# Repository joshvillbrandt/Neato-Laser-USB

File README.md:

Neato-Laser-USB
===============

A small PCB to run the Neato XV-11 laser scanner from USB.

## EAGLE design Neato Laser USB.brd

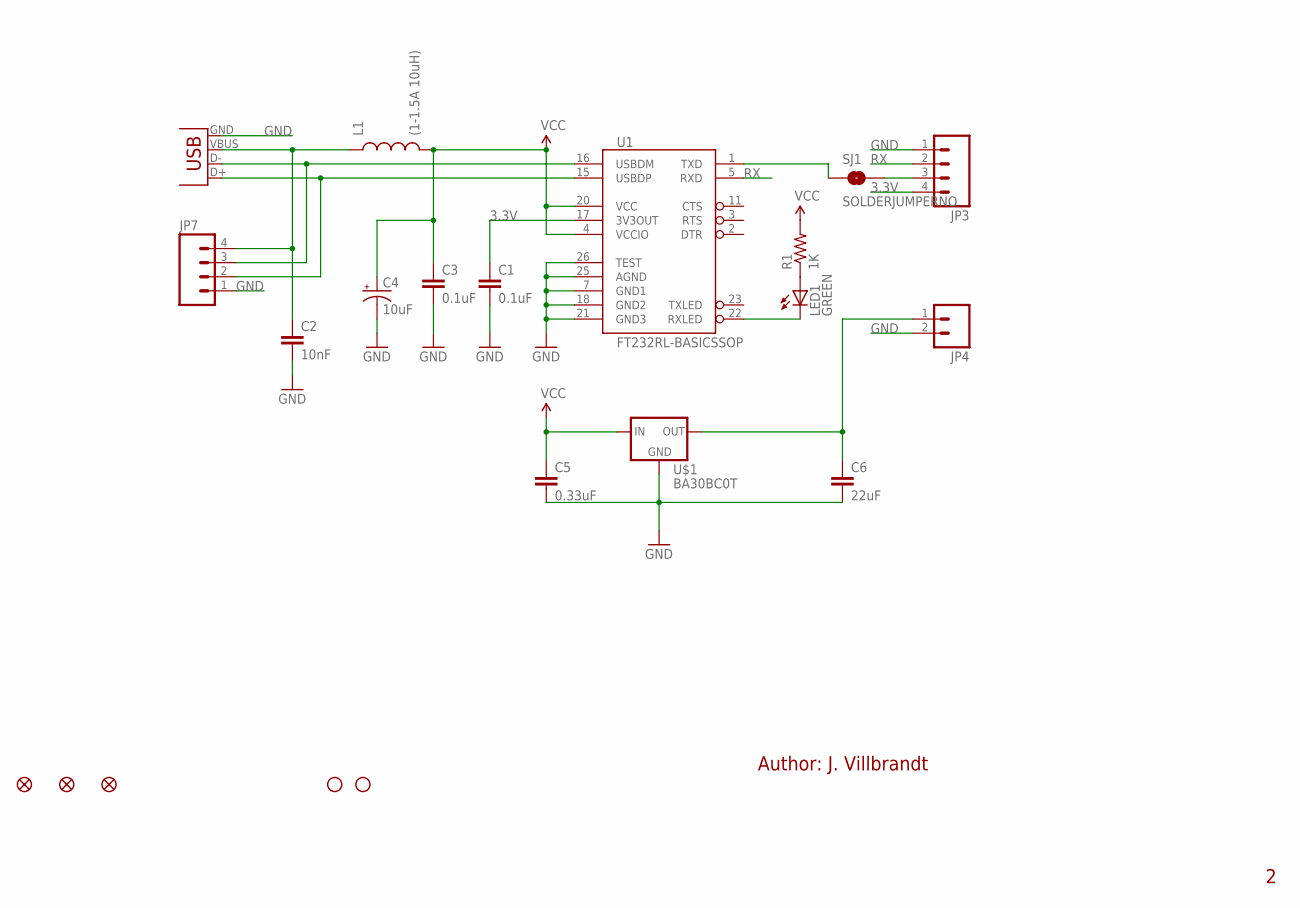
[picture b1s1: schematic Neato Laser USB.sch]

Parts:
C1, C3: 0.1uF; 0603-CAP
C2: 10nF; 0603-CAP
C4: 10uF; EIA3216
C5: 0.33uF; 0603-CAP
C6: 22uF; 0603-CAP
JP1, JP2: STAND-OFF
JP3: M04JST-PTH; JST-4-PTH
JP4: M02JST-PTH-2; JST-2-PTH
JP5, JP6, JP8: FIDUCIAL1X2.5; FIDUCIAL-1X2.5
JP7: M04PTH; 1X04
L1: (1-1.5A 10uH); 0603
LED1: GREEN; LED-0603
R1: 1K; 0402-RES
SJ1: SOLDERJUMPERNO; SJ_2S-NO
U1: FT232RL-BASICSSOP; SSOP28DB
U$1: BA30BC0T; 78XXL
X1: USBSMD; USB-MINIB

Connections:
3.0V: C6.1, JP4.1, U$1.OUT
3.3V: C1.1, JP3.4, U1.17 (3V3OUT)
GND: C1.2, C2.2, C3.2, C4.C (-), C5.2, C6.2, JP3.1, JP4.2, JP7.1, U1.7 (GND1), U1.18 (GND2), U1.21 (GND3), U1.25 (AGND), U1.26 (TEST), U$1.GND, X1.GND
unnamed: JP7.3, U1.16 (USBDM), X1.D-
unnamed: JP7.2, U1.15 (USBDP), X1.D+
unnamed: C2.1, JP7.4, L1.1, X1.VBUS
unnamed: LED1.C, U1.22 (RXLED)
unnamed: LED1.A, R1.1
unnamed: JP3.3, SJ1.2
unnamed: SJ1.1, U1.1 (TXD)
RX: JP3.2, U1.5 (RXD)
VCC: C3.1, C4.A (+), C5.1, L1.2, R1.2, U1.4 (VCCIO), U1.20 (VCC), U$1.IN

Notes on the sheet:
Author: J. Villbrandt

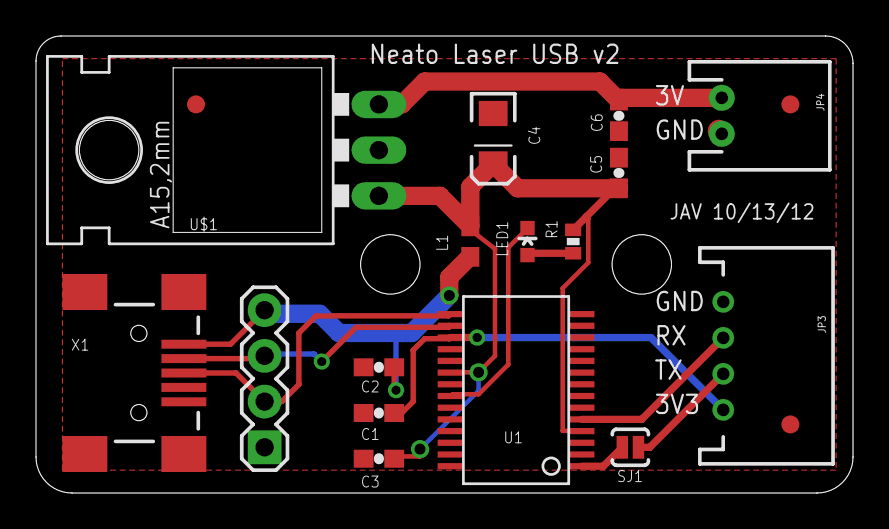
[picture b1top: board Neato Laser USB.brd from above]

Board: 2 copper layers, 45.4 x 25.4 mm, 21 parts (0 on the bottom side), 12 nets.

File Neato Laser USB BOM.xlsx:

Part | Value | Device | Package | Description | Digi-Key PN | Price
C1 | 0.1uF | CAP0603-CAP | 0603-CAP | Capacitor | 445-1316-1-ND | 1.0999999999999999E-2
C2 | 10nF | CAP0603-CAP | 0603-CAP | Capacitor | 445-5100-1-ND | 2.4E-2
C3 | 0.1uF | CAP0603-CAP | 0603-CAP | Capacitor | 445-1316-1-ND | 1.0999999999999999E-2
C4 | 10uF | CAP_POL1206 | EIA3216 | Capacitor Polarized | T491A106K010AT | 3.7999999999999999E-2
C5 | 0.33uF | CAP0603-CAP | 0603-CAP | Capacitor | 445-5142-1-ND | 7.4999999999999997E-2
C6 | 22uF | CAP0603-CAP | 0603-CAP | Capacitor | 445-8030-1-ND | 0.33600000000000002
JP1 | STAND-OFF | STAND-OFF | STAND-OFF | Stand Off | DNP | 0
JP2 | STAND-OFF | STAND-OFF | STAND-OFF | Stand Off | DNP | 0
JP3 |  | M04JST-PTH | JST-4-PTH | Header 4 | 455-1721-ND | 0.19800000000000001
JP4 |  | M02JST-PTH-2 | JST-2-PTH | Header 2 | 455-1719-ND | 0.153
JP5 | FIDUCIAL1X2.5 | FIDUCIAL1X2.5 | FIDUCIAL-1X2.5 | Fiducial Alignment Points | DNP | 0
JP6 | FIDUCIAL1X2.5 | FIDUCIAL1X2.5 | FIDUCIAL-1X2.5 | Fiducial Alignment Points | DNP | 0
JP7 |  | M04PTH | 1X04 | Header 4 | DNP | 0
JP8 | FIDUCIAL1X2.5 | FIDUCIAL1X2.5 | FIDUCIAL-1X2.5 | Fiducial Alignment Points | DNP | 0
L1 | (1-1.5A 10uH) | INDUCTOR0603 | 0603 | Inductors | 587-1720-1-ND | 0
LED1 | GREEN | LED0603 | LED-0603 | LEDs | 475-1409-1-ND | 7.3999999999999996E-2
R1 | 1K | RESISTOR0402-RES | 0402-RES | Resistor | 311-1.0KJRCT-ND | 0.1
SJ1 | SOLDERJUMPERNO | SOLDERJUMPERNO | SJ_2S-NO | Solder Jumper | DNP | 0
U$1 | BA30BC0T | BA30BC0T | 78XXL | LD1117VXX voltage regulator. We carry the 3.3V version (COM-00526) in TO-220 pa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 | BA30BC0T-ND | 1.72
U1 | FT232RL-BASICSSOP | FT232RL-BASICSSOP | SSOP28DB | USB UART | 768-1007-1-ND | 4.5
X1 | USBSMD | USBSMD | USB-MINIB | USB Connectors | ED2992CT-ND | 0.68
Total |  |  |  |  |  | 7.92

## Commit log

2013-12-19 initial commit from svn

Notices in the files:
parts and their libraries:
SparkFun: Licensing: CC v3.0 Share-Alike You are welcome to use this library for commercial purposes.
